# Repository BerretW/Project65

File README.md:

# Project65 — SBC 65C02 IRQ BigBoard

A fully custom **W65C02-based single-board computer** featuring an 8-priority-level IRQ subsystem, three ISA-8 expansion slots, a PS/2 keyboard interface, RS-232 serial port, and a complete firmware stack — including an interactive OS with a RAM-disk filesystem. Accompanied by a **full-featured Rust emulator** with a terminal UI and an **FPGA VGA + audio controller** (`APARTS_BUS`) for Intel MAX 10.

---

## Features

- **CPU:** W65C02S @ up to 8 MHz (jumper-selectable from 32 MHz main oscillator)
- **Memory:** 64 KB total — 32 KB lower RAM + 32 KB upper RAM + 8 KB EEPROM ROM
- **Serial:** R6551 ACIA with a 1.8432 MHz crystal for accurate baud rates
- **Parallel I/O:** 2× W65C22S VIA controllers (keyboard polling + parallel port)
- **PS/2 Keyboard:** ATtiny26 co-processor bridge
- **Interrupt system:** 74HC148 priority encoder + 74HC574 latch — 8 prioritized IRQ lines + NMI
- **Expansion:** 3× ISA-8 slots (TMS9918A, GameDuino, APARTS_BUS FPGA card)
- **FPGA video/audio:** `APARTS_BUS` — VGA 640×480, external SRAM framebuffer, font RAM, 4-ch DDS/ADSR → PCM5102A I²S
- **Firmware:** Two build targets — minimal bootloader and full AppartusOS
- **Emulator:** Rust TUI emulator (`p65emu`) with cycle-accurate peripherals

---

## Repository Structure

```text
Project65/
├── Eagle/              # PCB schematics and board layouts (Eagle CAD)
│   ├── SBC_65C02_IRQ_BigBoard_v10-2-1.*
│   ├── EXP_TMS9918A_V1.*
│   └── EXP_GameDuino_V1.*
├── Firmware/           # 65C02 firmware (cc65 / ca65 toolchain)
│   ├── src/            # Assembly + C sources (drivers, OS, shell, EWOZ)
│   │   └── os/         # AppartusOS modules
│   ├── config/         # ld65 linker configurations
│   ├── output/         # Build artifacts (*.bin, *.map)
│   ├── build_minimal.bat
│   └── build_appartus.bat
├── emulator/           # Rust emulator (p65emu)
│   └── src/            # cpu, bus, ram, rom, acia, via, irq_latch, tui
├── aprts_vga/          # APARTS_BUS FPGA RTL (Verilog) + Quartus + sim
│   ├── aprts_bus.v     # Top-level 6502 bus interface
│   ├── vga_timing.v    # VGA 640×480 @ 60 Hz timing (25 MHz)
│   ├── vga_video_gen.v # Graphics/text pixel path + font RAM
│   ├── sram_controller.v
│   ├── aprts_audio.v   # 4-ch DDS/ADSR + I²S (PCM5102A)
│   ├── 10M02_test.qsf  # Quartus project (MAX 10 10M02SCE144C8G)
│   └── sim/            # ModelSim / Icarus testbenches
├── GAL/                # Glue logic (PLD)
├── tools/
│   ├── uploader.py     # Python/tkinter firmware uploader (COM or TCP)
│   ├── aprts_vga/      # 6502 demo for FPGA VGA
│   ├── audio/          # Audio driver + samples (ca65)
│   └── …               # hello, mem_mon, vera_test, vga_test, …
└── CLAUDE.md           # Full hardware reference (address map, ICs, bugs)
```

---

## Hardware Overview

| Reference | Part | Description |
| --------- | ---- | ----------- |
| IC4 | W65C02SP | Main CPU (CMOS 65C02, DIP-40) |
| IC5 | AT28C64B | 8 KB EEPROM — ROM (`$E000–$FFFF`) |
| IC6 | 62256 | 32 KB SRAM — lower RAM (`$0000–$7FFF`) |
| IC7 | 62256 | 32 KB SRAM — upper RAM (`$8000–$BFFF`) |
| IC8 | DS1233 | Power-on reset supervisor |
| IC16 | W65C22S6TP | VIA #2 (`$CC80`) — parallel port JP8, generates **IRQ1** |
| IC18 | W65C22S6TP | VIA #1 (`$CC00`) — ATtiny26 keyboard bridge, generates **NMI** |
| IC19 | R6551 | ACIA serial (`$C800–$CBFF`) |
| IC14 | ATtiny26 | PS/2 keyboard co-processor (PB3=CLK, PB4=DATA) |
| U$1 | MCP2221A | USB-C ↔ UART/I²C bridge |
| IC9/IC11 | 74HCT139N | Two-stage address decoder |
| IC17 | 74HC148N | 8→3 priority IRQ encoder |
| IC27 | 74HC574N | IRQ status latch (readable at `$C480`) |
| QG1 | 32 MHz | Main system oscillator |
| Q1 | 1.8432 MHz | ACIA baud-rate crystal |
| X1–X3 | ISA-8 slots | Three 8-bit ISA expansion slots |

### ISA Expansion Cards

| Card | Description |
| ---- | ----------- |
| `EXP_TMS9918A_V1` | TMS9918A video card |
| `EXP_GameDuino_V1` | GameDuino graphics card |
| **APARTS_BUS** (`aprts_vga/`) | FPGA VGA 640×480 + external SRAM + 4-ch audio (MAX 10) |

---

## Address Map

```text
$0000–$7FFF   IC6 SRAM — lower 32 KB       (!CS = A15 low)
$8000–$BFFF   IC7 SRAM — upper 32 KB       (!CS = !HRAM_CS)
$C000–$C3FF   VERA / ISA video             (!VERA_CS)
$C400–$C7FF   IRQ latch                    read $C480–$C4FF / ack $C400–$C47F
$C800–$CBFF   ACIA R6551
$CC00–$CC7F   VIA1 (IC18) — keyboard/NMI
$CC80–$CCFF   VIA2 (IC16) — parallel/IRQ1
$CD00–$CDFF   ISA DEV0
$CE00–$CEFF   ISA DEV1
$CF00–$CFFF   ISA DEV2   ← typical APARTS_BUS decode (tools use $CF00 / $CE00)
$D000–$DFFF   ISA extended
$E000–$FFFF   EEPROM ROM (8 KB)
```

### IRQ Priority Table

| Level | Signal | Source |
| ----- | ------ | ------ |
| 0 (highest) | IRQ0 | R6551 ACIA |
| 1 | IRQ1 | VIA2 (IC16, `$CC80`) |
| 2–6 | IRQ2–6 | ISA slots |
| 7 (lowest) | IRQ7 | Button S1 |
| — | **NMI** | **VIA1 (IC18, `$CC00`)** |

---

## APARTS_BUS — FPGA VGA & Audio (`aprts_vga/`)

RTL controller for the 6502/ISA bus: **VGA output**, **external SRAM framebuffer (up to 512 KB / 19-bit address)**, **internal font RAM**, and a **4-channel synthesizer** driving a **PCM5102A** over I²S.

Detailed programmer manual: [`aprts_vga/README.md`](aprts_vga/README.md).

### Target & RTL modules

| Item | Value |
| ---- | ----- |
| FPGA | Intel **MAX 10** — `10M02SCE144C8G` |
| Quartus project | `aprts_vga/10M02_test.qsf` |
| Top entity | `aprts_bus` |
| Pixel clock | **25 MHz** — VGA **640×480 @ 60 Hz** |

| File | Module | Role |
| ---- | ------ | ---- |
| `aprts_bus.v` | `aprts_bus` | Top: 4-bit port decode, CPU R/W, submodule wiring |
| `vga_timing.v` | `vga_timing` | H/V counters, HSYNC/VSYNC, `video_on` |
| `vga_video_gen.v` | `vga_video_gen` | Graphics/text RGB, font RAM (128×8 = 1024 B), cursor blink |
| `sram_controller.v` | `sram_controller` | CPU ↔ VGA arbiter, hardware clear engine |
| `aprts_audio.v` | `aprts_audio` | 4-ch DDS + ADSR, I²S (`pcm_bck` / `pcm_din` / `pcm_lrck`) |

### External interfaces (from `aprts_bus`)

```text
6502 bus:   n_reset, n_mem_w, n_mem_r, lv_cs, clk, lv_addr[3:0], lv_data[7:0]
VGA:        red[2:0], green[2:0], blue[2:0], hsync, vsync
SRAM:       sram_addr[18:0], sram_data[7:0], sram_ce_n, sram_oe_n, sram_we_n
Audio I²S:  pcm_bck, pcm_din, pcm_lrck, pcm_sck
```

### Register map (ports `$0`–`$F` relative to card base)

| Port | Write | Read |
| ---- | ----- | ---- |
| `$0` | Background color RGB332 | `reg_bg_color` |
| `$1` | Address / cursor hi (`addr_hi`) | same |
| `$2` | Address mid (`addr_mid`) | same |
| `$3` | Address lo (`addr_lo`) | same |
| `$4` | Data → SRAM / font / text cell | Data ← SRAM / font |
| `$5` | Audio register index (`0x00`–`0x17`) | current index |
| `$6` | Audio register data (index auto-inc) | selected audio reg |
| `$D` | Mode | current mode |
| `$F` | Start SRAM clear (any value) | status: bit0 = `addr_ready` |

CPU SRAM pointer is 19-bit: `{addr_hi[2:0], addr_mid, addr_lo}`. After each write to port `$4` (except font mode `$0D`) the address **auto-increments**.

**Background / pixel color:** `[7:5]` R, `[4:2]` G, `[1:0]` B (expanded to 3 bits in HW).

### Mode register (`$D`)

| Value | Behavior |
| ----- | -------- |
| `$00`–`$0C` | Graphics — linear framebuffer from external SRAM |
| `$01` | Text 80×60, static cursor |
| `$02` | Text 80×60, blinking cursor (~2 Hz) |
| `$0D` | Font edit — R/W internal `font_mem` via port `$4` |
| `$0E` | Hardware logic reset (counters, audio, registers) |
| `$0F` | Blank screen (force black) |

Text buffer uses the first **4800** bytes of SRAM (`80×60`, `$0000`–`$12BF`). Font RAM: **128 characters × 8 rows**.

### SRAM clear & status (`$F`)

- **Write:** starts hardware fill of external SRAM with zeros (clear range through `$4AFFF` in RTL).
- **Read bit 0 (`addr_ready`):** `1` = ready for CPU access; `0` = clear/write busy. Poll before further writes.

### Audio (ports `$5` / `$6`)

Four independent DDS channels mixed to I²S (PCM5102A). Sample rate in driver notes: **~48.828 kHz**.

Per channel (base offsets for ch0; +3 per channel for ch1–3):

| Index | Register |
| ----- | -------- |
| `+0` / `+1` | Frequency lo / hi |
| `+2` | Volume |
| `$0C`–`$0F` | Control: wave `[2:0]`, ADSR enable `[3]`, gate/note-on `[4]` |
| `$10`–`$17` | ADSR Attack/Decay and Sustain/Release pairs |

Waveforms: `0` square, `1` triangle, `2` saw, `3` sine, `4` trapezoid. Writing `$6` auto-increments the audio index.

### Simulation (`aprts_vga/sim/`)

| File | Purpose |
| ---- | ------- |
| `tb_aprts_bus.v` | Integration test of full `aprts_bus` |
| `tb_vga_timing.v` | VGA timing unit test |
| `tb_aprts_audio.v` | Audio registers + I²S clocks |
| `sram_model.v` | Behavioral 512 KB SRAM |
| `run_msim.bat` / `run_msim.do` | ModelSim / Questa-Intel |
| `run_iverilog.bat` | Icarus Verilog |

```bat
cd aprts_vga\sim
run_msim.bat
rem or: run_iverilog.bat
```

See [`aprts_vga/sim/README.md`](aprts_vga/sim/README.md).

### Host-side tools

| Path | Description |
| ---- | ----------- |
| `tools/aprts_vga/` | ca65 demo (`demo.asm`) — base often `$CF00` |
| `tools/audio/` | Audio includes (`audio.inc65`) and samples — ports `$5`/`$6` on card base |

Exact ISA slot base (`$CD00` / `$CE00` / `$CF00`) depends on which DEV chip-select the card is wired to.

---

## Firmware

### Prerequisites

- [cc65](https://cc65.github.io/) toolchain (`cc65`, `ca65`, `ld65`) on `PATH`

### Minimal Build

ACIA serial + EWOZ (WozMon) monitor + serial bootloader (loads to `$6000`).  
No keyboard, VDP, SPI, SD, GameDuino, or SAA1099 dependencies.

```bat
cd Firmware
build_minimal.bat
```

Output: `Firmware/output/MIN_ROM.bin` (8 KB, write to EEPROM IC5)

### AppartusOS Build

Full OS: ACIA + EWOZ (`MON` command) + Intel HEX loader + interactive shell + RAM-disk FS.

```bat
cd Firmware
build_appartus.bat
```

Output: `Firmware/output/APPARTUS_OS.bin` (8 KB, write to EEPROM IC5)

### AppartusOS Shell Commands

```text
HELP / ?                   — help
VER                        — OS version
DIR                        — list RAM-disk files
FREE                       — show free space
FORMAT                     — reinitialize RAM disk (requires Y confirmation)
LOAD                       — receive Intel HEX via ACIA
SAVE <name> <addr> <size>  — save RAM region to RAM disk (hex addresses)
DEL  <name>                — delete file
RUN  <name>                — execute file (program can RTS back to shell)
MON                        — EWOZ / WozMon monitor
RESET                      — soft reset ($FF00)
```

### RAM Disk Layout (`$6000–$BFFF`, 24 KB)

```text
$6000–$600F   Header: "APOS" + num_files + free_ptr
$6010–$610F   Directory: 16 entries × 16 bytes
              +0 name[8]  +8 load_addr  +10 size  +12 flags  +13 stor_addr
$6110–$BFFF   File data (~24 KB usable)
```

### Firmware Memory Map (ROM, `$E000–$FFFF`)

```text
ZP:      $0000–$00FF   (zero page; cc65 $00–$1F, EWOZ $24–$30, ihex $38–$3E, OS $40–$4E)
RAM:     $0200–$5FFF   (working RAM; stack at $5FFF growing down)
ROM:     $E000–$FFFF   (EEPROM, fill $FF)
JMPTBL:  $FF00         (BIOS-style jump table)
VECTORS: $FFFA         (NMI / RESET / IRQ vectors)
```

---

## Emulator — p65emu

A cycle-accurate Rust emulator with a ratatui terminal UI.

### Build Requirements

- [Rust toolchain](https://rustup.rs/) (stable)

### Build & Run

```sh
cargo run --manifest-path emulator/Cargo.toml -- [ROM.bin] [-s SPEED_HZ] [-p TCP_PORT]
```

| Flag | Default | Description |
| ---- | ------- | ----------- |
| `ROM.bin` | — | ROM image to load at `$E000` |
| `-s SPEED_HZ` | `1000000` | Emulation speed in Hz |
| `-p TCP_PORT` | `6551` | TCP serial port (0 = disabled) |
| `--family` | `HCT` | Logic family timing model (`LS`, `ALS`, `HCT`, `HC`, `AC`, `ACT`) |

### Emulated Components

| Module | Hardware |
| ------ | -------- |
| `cpu.rs` | W65C02 — fetch/decode/execute + NMI/IRQ |
| `ram.rs` | IC6 + IC7 SRAM |
| `rom.rs` | 8 KB EEPROM |
| `acia.rs` | R6551 — TX/RX queues shared with TUI and TCP |
| `via.rs` | VIA1 (`$CC00`) + VIA2 (`$CC80`) — T1/T2 timers |
| `irq_latch.rs` | 74HC574 latch + 74HC148 encoder |
| `tms9918a.rs` | TMS9918A video (minifb window) |
| `saa1099.rs` | SAA1099 audio (rodio) |

### TUI Keyboard Shortcuts

| Key | Action |
| --- | ------ |
| F2 | Single step |
| F3 | Run / Pause |
| F4 | Reset CPU |
| F5–F9 | Speed: 1K / 10K / 100K / 1M / MAX Hz |
| +/- | Speed ×2 / ÷2 |
| Tab | Memory view: ZP / RAM / HiRAM / I/O / ROM / Addr |
| Shift+Tab | Right panel: CPU / VIA1 / VIA2 / ACIA / IRQ |
| PgUp/PgDn | Scroll memory |
| Shift+Pg | Scroll terminal |
| Ctrl+O | File browser — load ROM or RAM image |
| Ctrl+G | Jump to hex address in memory dump |
| Ctrl+M | Edit byte at address |
| Ctrl+R | Edit CPU registers (A/X/Y/SP/PC/P) |
| F10 / Ctrl+Q | Quit |

The TCP serial port (default `127.0.0.1:6551`) allows PuTTY, netcat, or `uploader.py` to connect as if it were real hardware.

---

## Tools

### tools/uploader.py

Python/tkinter GUI for uploading firmware to the real board or the emulator.

**Dependencies:**

```sh
pip install pyserial
```

**Connection modes:**

- **COM port** — real hardware (19200 Bd, 8N1)
- **TCP** — emulator (`127.0.0.1:6551`)

**Bootloader protocol:**

| Command | Action |
| ------- | ------ |
| `w` | Raw binary upload — exactly 8192 bytes → `$6000–$7FFF` |
| `h` | Intel HEX upload (any address) |
| `s` | Jump to `$6000` (run program) |
| `m` | Enter EWOZ / WozMon monitor |
| `^R` (`$12`) | Soft-restart bootloader |

### Other tools

| Path | Description |
| ---- | ----------- |
| `tools/aprts_vga/` | APARTS_BUS VGA demo for AppartusOS |
| `tools/audio/` | 4-channel FPGA audio driver and samples |
| `tools/hello/` | Sample user program |
| `tools/ihex_gen.py` | Intel HEX helper |
| `tools/espi_update_fpga.py` | FPGA update helper |
| `tools/vera_test/`, `tools/vga_test/` | Video experiments |

---

## Typical Workflow

```sh
# 1. Build firmware
cd Firmware && build_appartus.bat

# 2. Start emulator
cargo run --manifest-path emulator/Cargo.toml -- Firmware/output/APPARTUS_OS.bin

# 3. In emulator terminal — send a program via Intel HEX
> LOAD
  (paste or send .hex file via uploader.py over TCP)

# 4. Save and run
> SAVE HELLO 6090 0100
> DIR
> RUN HELLO
```

FPGA RTL / sim workflow:

```bat
cd aprts_vga\sim
run_msim.bat
```

---

## Known Issues

| # | Status | Description |
| - | ------ | ----------- |
| 1 | ✅ Fixed | `_nmi_init` in `utils.asm` — NMI Timer1 initialization correctly configures VIA1 (IC18) at $CC00 |
| 2 | ✅ Fixed | NMI ISR correctly reloads VIA1 (IC18) T1 counter — verified in `interrupts.asm:19` |
| 3 | ✅ Fixed | PS/2 keyboard driver in `pckybd.asm:25–28` — now correctly reads from VIA1 (IC18, ATtiny26) |
| 4 | ✅ Fixed | `VDP_MODE0 = $C000` — correctly placed in ISA I/O space, no longer conflicts with IC6 RAM |

All critical hardware bugs have been resolved.

---

## Hardware Files

| File | Description |
| ---- | ----------- |
| `Eagle/SBC_65C02_IRQ_BigBoard_v10-2-1.csv` | Current BOM / netlist |
| `Eagle/SBC_65C02_IRQ_BigBoard_v9-1-3.sch` | Main schematic (Eagle) |
| `Eagle/SBC_65C02_IRQ_BigBoard_v9-1-3.brd` | Main PCB layout (Eagle) |
| `Eagle/EXP_TMS9918A_V1.sch/.brd` | TMS9918A ISA video card |
| `Eagle/EXP_GameDuino_V1.sch/.brd` | GameDuino ISA graphics card |
| `aprts_vga/*.v` | APARTS_BUS FPGA RTL (VGA + SRAM + audio) |
| `aprts_vga/10M02_test.qsf` | Quartus pinout / project for MAX 10 |

Full hardware documentation (address decoding logic, IC cross-reference, IRQ system) is in [`CLAUDE.md`](CLAUDE.md).  
FPGA register-level docs: [`aprts_vga/README.md`](aprts_vga/README.md).

---

## License

See [`Firmware/LICENSE`](Firmware/LICENSE).

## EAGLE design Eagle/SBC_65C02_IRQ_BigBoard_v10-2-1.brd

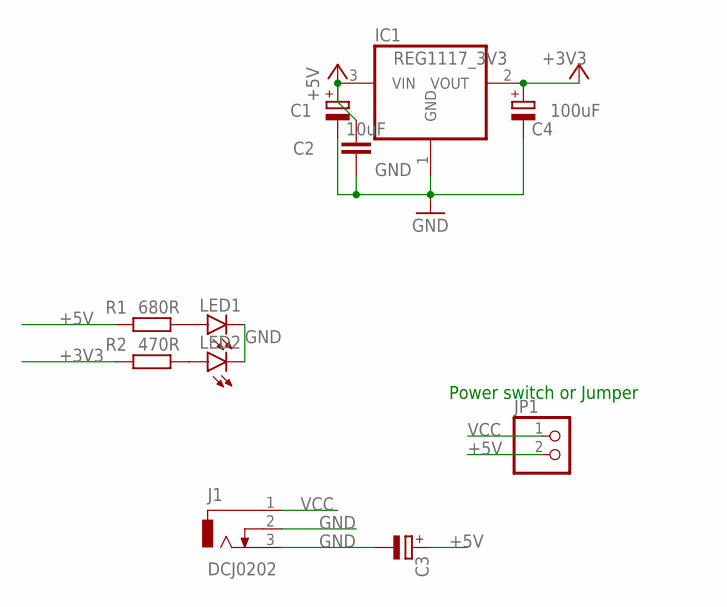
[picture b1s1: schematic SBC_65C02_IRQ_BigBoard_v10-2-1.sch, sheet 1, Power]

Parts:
C1: 10uF; E2,5-5
C2: C-EU050-035X075; C050-035X075
C3: CPOL-EUE2.5-5; E2,5-5
C4: 100uF; E2,5-5
IC1: REG1117_3V3; SOT223
J1: DCJ0202
JP1: PINHD-1X2; 1X02
LED1, LED2: LED5MM
R1: 680R; 0207/10
R2: 470R; 0207/10

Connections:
+3V3: C4.+, IC1.2 (VOUT), R2.2
+5V: C1.+, C2.1, C3.+, IC1.3 (VIN), JP1.2, R1.2; also elsewhere on the board
GND: C1.-, C2.2, C3.-, C4.-, IC1.1 (GND), J1.2, J1.3, LED1.K (C), LED2.K (C); also elsewhere on the board
unnamed: LED1.A, R1.1
unnamed: LED2.A, R2.1
VCC: J1.1, JP1.1

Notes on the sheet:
Power switch or Jumper

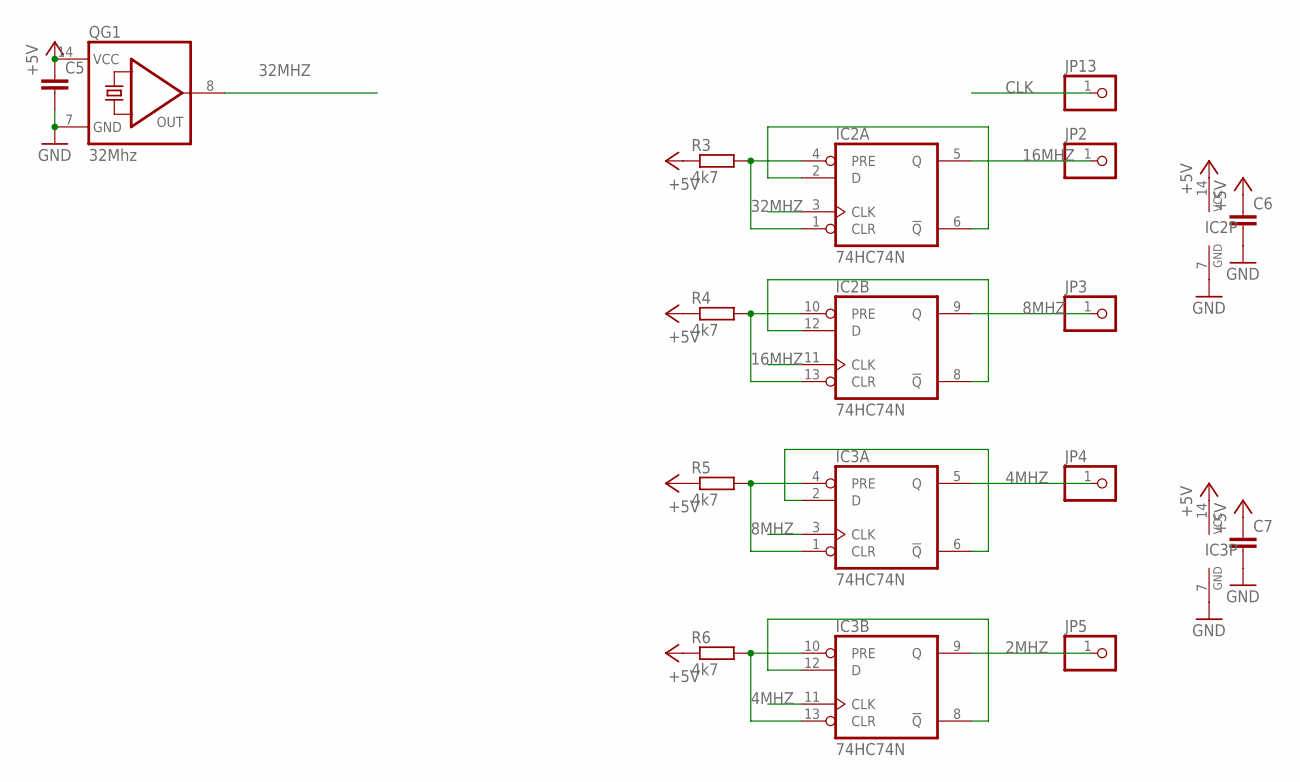
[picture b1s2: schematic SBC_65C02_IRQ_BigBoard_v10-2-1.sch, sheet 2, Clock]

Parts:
C5, C6, C7: C-EU050-025X075; C050-025X075
IC2, IC3: 74HC74N; DIL14
JP2, JP3, JP4, JP5, JP13: PINHD-1X1; 1X01
QG1: 32Mhz; DIL14S
R3, R4, R5, R6: 4k7; 0204/7

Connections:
2MHZ: IC3.9 (Q), JP5.1
4MHZ: IC3.5 (Q), IC3.11 (CLK), JP4.1
8MHZ: IC2.9 (Q), IC3.3 (CLK), JP3.1
16MHZ: IC2.5 (Q), IC2.11 (CLK), JP2.1
32MHZ: IC2.3 (CLK), QG1.8 (OUT); also elsewhere on the board
+5V: C5.1, C6.1, C7.1, IC2.14 (VCC), IC3.14 (VCC), QG1.14 (VCC), R3.1, R4.1, R5.1, R6.1; also elsewhere on the board
CLK: JP13.1; also elsewhere on the board
GND: C5.2, C6.2, C7.2, IC2.7 (GND), IC3.7 (GND), QG1.7 (GND); also elsewhere on the board
unnamed: IC2.2 (D), IC2.6 (!Q)
unnamed: IC2.8 (!Q), IC2.12 (D)
unnamed: IC2.1 (CLR), IC2.4 (PRE), R3.2
unnamed: IC2.10 (PRE), IC2.13 (CLR), R4.2
unnamed: IC3.2 (D), IC3.6 (!Q)
unnamed: IC3.1 (CLR), IC3.4 (PRE), R5.2
unnamed: IC3.8 (!Q), IC3.12 (D)
unnamed: IC3.10 (PRE), IC3.13 (CLR), R6.2

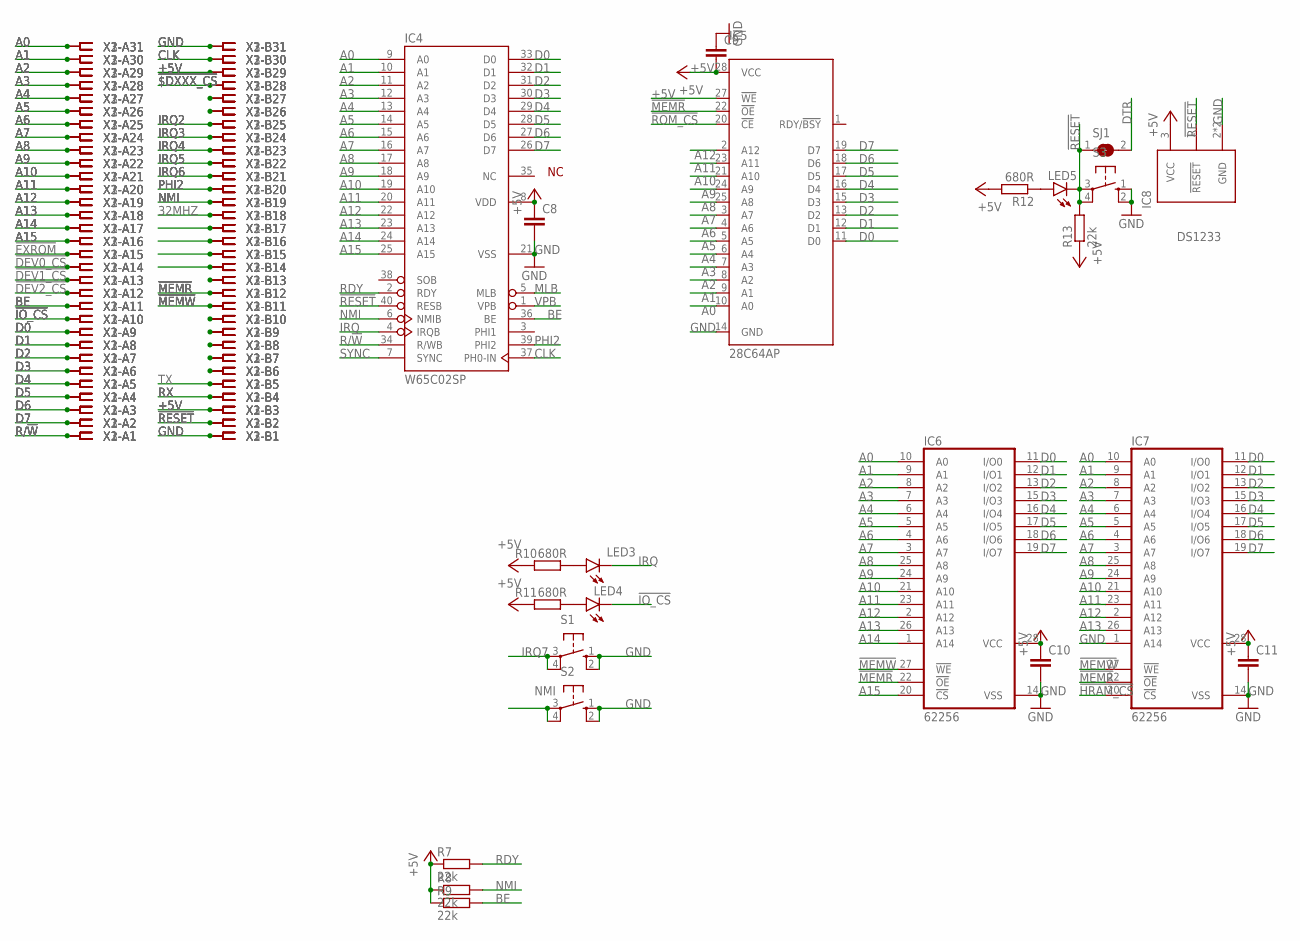
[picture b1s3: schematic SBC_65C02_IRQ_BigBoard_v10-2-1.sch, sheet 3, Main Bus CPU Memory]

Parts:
C8, C9, C10, C11: C-EU050-025X075; C050-025X075
IC4: W65C02SP; DIL40
IC5: 28C64AP; DIL28-6
IC6, IC7: 62256; DIL28-6
IC8: DS1233; SOT223
LED3, LED4, LED5: LED5MM
R7, R8, R9, R13: 22k; 0207/10
R10, R11, R12: 680R; 0207/10
S1, S2, S3: 10-XX; B3F-10XX
SJ1: SJ
X1, X2, X3: ISA-SLOT; ISA-8

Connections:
32MHZ: X1.B18, X2.B18, X3.B18; also elsewhere on the board
!$DXXX_CS: X1.B28, X2.B28, X3.B28; also elsewhere on the board
!DEV0_CS: X1.A14, X2.A14, X3.A14; also elsewhere on the board
!DEV1_CS: X1.A13, X2.A13, X3.A13; also elsewhere on the board
!DEV2_CS: X1.A12, X2.A12, X3.A12; also elsewhere on the board
!EXROM: X1.A15, X2.A15, X3.A15; also elsewhere on the board
!HRAM_CS: IC7.20 (!CS); also elsewhere on the board
!IO_CS: LED4.K (C), X1.A10, X2.A10, X3.A10; also elsewhere on the board
!MEMR: IC5.22 (!OE), IC6.22 (!OE), IC7.22 (!OE), X1.B12, X2.B12, X3.B12; also elsewhere on the board
!MEMW: IC6.27 (!WE), IC7.27 (!WE), X1.B11, X2.B11, X3.B11; also elsewhere on the board
!RESET: IC4.40 (RESB), IC8.1 (!RESET), LED5.K (C), R13.2, S3.3, S3.4 (P1), SJ1.1, X1.B2, X2.B2, X3.B2; also elsewhere on the board
!ROM_CS: IC5.20 (!CE); also elsewhere on the board
+5V: C8.1, C9.2, C10.1, C11.1, IC4.8 (VDD), IC5.27 (!WE), IC5.28 (VCC), IC6.28 (VCC), IC7.28 (VCC), IC8.3 (VCC), R7.1, R8.1, R9.1, R10.2, R11.2, R12.2, R13.1, X1.B3, X1.B29, X2.B3, X2.B29, X3.B3, X3.B29; also elsewhere on the board
A0: IC4.9 (A0), IC5.10 (A0), IC6.10 (A0), IC7.10 (A0), X1.A31, X2.A31, X3.A31; also elsewhere on the board
A1: IC4.10 (A1), IC5.9 (A1), IC6.9 (A1), IC7.9 (A1), X1.A30, X2.A30, X3.A30; also elsewhere on the board
A2: IC4.11 (A2), IC5.8 (A2), IC6.8 (A2), IC7.8 (A2), X1.A29, X2.A29, X3.A29; also elsewhere on the board
A3: IC4.12 (A3), IC5.7 (A3), IC6.7 (A3), IC7.7 (A3), X1.A28, X2.A28, X3.A28; also elsewhere on the board
A4: IC4.13 (A4), IC5.6 (A4), IC6.6 (A4), IC7.6 (A4), X1.A27, X2.A27, X3.A27; also elsewhere on the board
A5: IC4.14 (A5), IC5.5 (A5), IC6.5 (A5), IC7.5 (A5), X1.A26, X2.A26, X3.A26
A6: IC4.15 (A6), IC5.4 (A6), IC6.4 (A6), IC7.4 (A6), X1.A25, X2.A25, X3.A25
A7: IC4.16 (A7), IC5.3 (A7), IC6.3 (A7), IC7.3 (A7), X1.A24, X2.A24, X3.A24; also elsewhere on the board
A8: IC4.17 (A8), IC5.25 (A8), IC6.25 (A8), IC7.25 (A8), X1.A23, X2.A23, X3.A23; also elsewhere on the board
A9: IC4.18 (A9), IC5.24 (A9), IC6.24 (A9), IC7.24 (A9), X1.A22, X2.A22, X3.A22; also elsewhere on the board
A10: IC4.19 (A10), IC5.21 (A10), IC6.21 (A10), IC7.21 (A10), X1.A21, X2.A21, X3.A21; also elsewhere on the board
A11: IC4.20 (A11), IC5.23 (A11), IC6.23 (A11), IC7.23 (A11), X1.A20, X2.A20, X3.A20; also elsewhere on the board
A12: IC4.22 (A12), IC5.2 (A12), IC6.2 (A12), IC7.2 (A12), X1.A19, X2.A19, X3.A19; also elsewhere on the board
A13: IC4.23 (A13), IC6.26 (A13), IC7.26 (A13), X1.A18, X2.A18, X3.A18; also elsewhere on the board
A14: IC4.24 (A14), IC6.1 (A14), X1.A17, X2.A17, X3.A17; also elsewhere on the board
A15: IC4.25 (A15), IC6.20 (!CS), X1.A16, X2.A16, X3.A16; also elsewhere on the board
BE: IC4.36 (BE), R9.2, X1.A11, X2.A11, X3.A11
CLK: IC4.37 (PH0-IN), X1.B30, X2.B30, X3.B30; also elsewhere on the board
CS_1: X1.B27, X2.B27, X3.B27
CS_2: X1.B26, X2.B26, X3.B26
D0: IC4.33 (D0), IC5.11 (D0), IC6.11 (I/O0), IC7.11 (I/O0), X1.A9, X2.A9, X3.A9; also elsewhere on the board
D1: IC4.32 (D1), IC5.12 (D1), IC6.12 (I/O1), IC7.12 (I/O1), X1.A8, X2.A8, X3.A8; also elsewhere on the board
D2: IC4.31 (D2), IC5.13 (D2), IC6.13 (I/O2), IC7.13 (I/O2), X1.A7, X2.A7, X3.A7; also elsewhere on the board
D3: IC4.30 (D3), IC5.15 (D3), IC6.15 (I/O3), IC7.15 (I/O3), X1.A6, X2.A6, X3.A6; also elsewhere on the board
D4: IC4.29 (D4), IC5.16 (D4), IC6.16 (I/O4), IC7.16 (I/O4), X1.A5, X2.A5, X3.A5; also elsewhere on the board
D5: IC4.28 (D5), IC5.17 (D5), IC6.17 (I/O5), IC7.17 (I/O5), X1.A4, X2.A4, X3.A4; also elsewhere on the board
D6: IC4.27 (D6), IC5.18 (D6), IC6.18 (I/O6), IC7.18 (I/O6), X1.A3, X2.A3, X3.A3; also elsewhere on the board
D7: IC4.26 (D7), IC5.19 (D7), IC6.19 (I/O7), IC7.19 (I/O7), X1.A2, X2.A2, X3.A2; also elsewhere on the board
DTR: SJ1.2; also elsewhere on the board
GND: C8.2, C9.1, C10.2, C11.2, IC4.21 (VSS), IC5.14 (GND), IC6.14 (VSS), IC7.1 (A14), IC7.14 (VSS), IC8.2 (GND), IC8.4 (GND), S1.1 (S), S1.2 (S1), S2.1 (S), S2.2 (S1), S3.1 (S), S3.2 (S1), X1.B1, X1.B31, X2.B1, X2.B31, X3.B1, X3.B31; also elsewhere on the board
IRQ: IC4.4 (IRQB), LED3.K (C); also elsewhere on the board
IRQ2: X1.B25, X2.B25, X3.B25; also elsewhere on the board
IRQ3: X1.B24, X2.B24, X3.B24; also elsewhere on the board
IRQ4: X1.B23, X2.B23, X3.B23; also elsewhere on the board
IRQ5: X1.B22, X2.B22, X3.B22; also elsewhere on the board
IRQ6: X1.B21, X2.B21, X3.B21; also elsewhere on the board
IRQ7: S1.3, S1.4 (P1); also elsewhere on the board
MLB: IC4.5 (MLB)
unnamed: LED3.A, R10.1
unnamed: LED5.A, R12.1
unnamed: X1.B6, X2.B6, X3.B6
unnamed: X1.B7, X2.B7, X3.B7
unnamed: X1.B8, X2.B8, X3.B8
unnamed: LED4.A, R11.1
unnamed: X1.B9, X2.B9, X3.B9
unnamed: X1.B10, X2.B10, X3.B10
unnamed: X1.B13, X2.B13, X3.B13
unnamed: X1.B14, X2.B14, X3.B14
NMI: IC4.6 (NMIB), R8.2, S2.3, S2.4 (P1), X1.B19, X2.B19, X3.B19; also elsewhere on the board
PHI2: IC4.39 (PHI2), X1.B20, X2.B20, X3.B20; also elsewhere on the board
R/!W: IC4.34 (R/WB), X1.A1, X2.A1, X3.A1; also elsewhere on the board
RDY: IC4.2 (RDY), R7.2
RX: X1.B4, X2.B4, X3.B4; also elsewhere on the board
SPI_MOSI: X1.B17, X2.B17, X3.B17
SPI_NSEL2: X1.B15, X2.B15, X3.B15
SPI_SCLK: X1.B16, X2.B16, X3.B16
SYNC: IC4.7 (SYNC)
TX: X1.B5, X2.B5, X3.B5; also elsewhere on the board
VPB: IC4.1 (VPB)

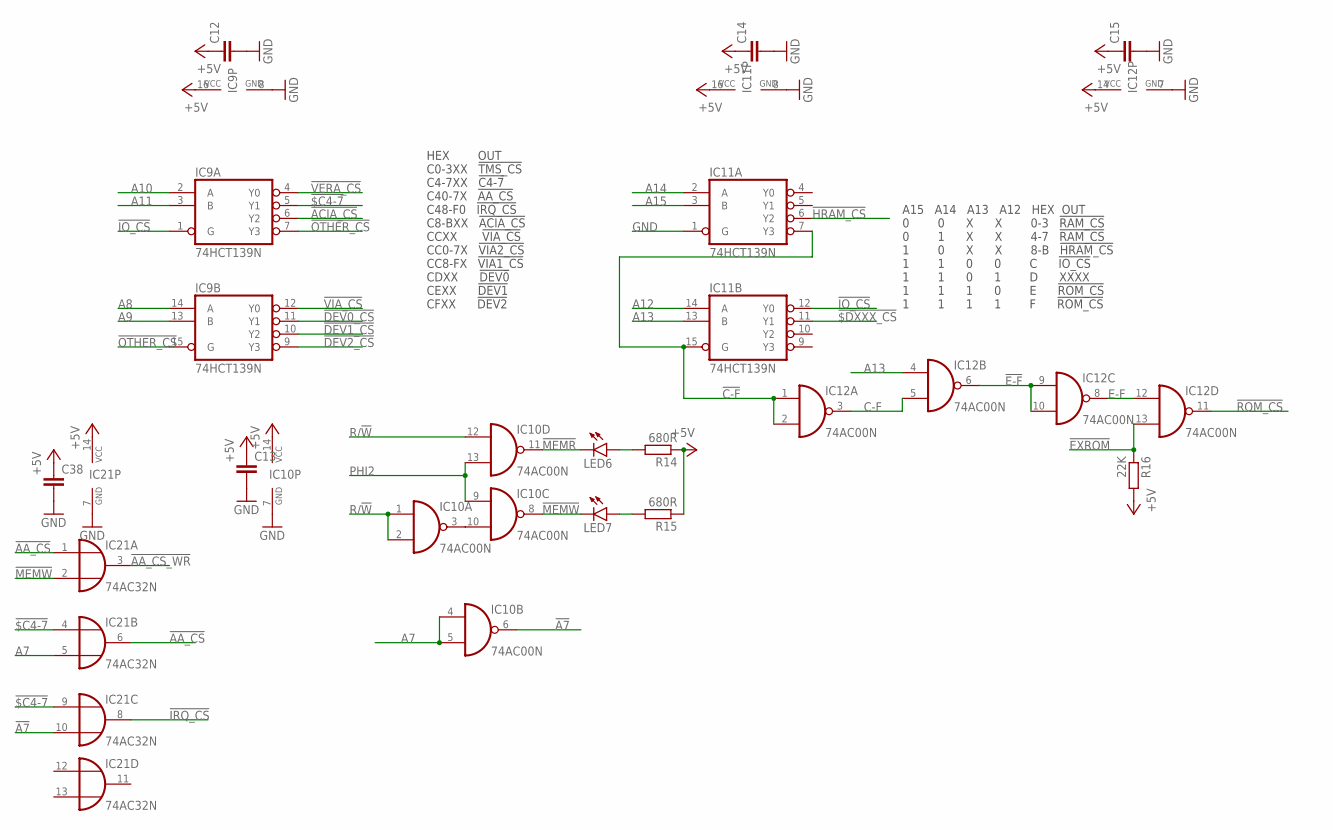
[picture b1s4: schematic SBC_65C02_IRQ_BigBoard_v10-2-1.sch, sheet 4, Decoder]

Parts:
C12, C13, C14, C15, C38: C-EU050-025X075; C050-025X075
IC9, IC11: 74HCT139N; DIL16
IC10, IC12: 74AC00N; DIL14
IC21: 74AC32N; DIL14
LED6, LED7: LED5MM
R14, R15: 680R; 0207/10
R16: 22K; 0207/10

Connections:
!$C4-7: IC9.5 (Y1), IC21.4 (I0), IC21.9 (I0)
!$DXXX_CS: IC11.11 (Y1); also elsewhere on the board
!A7: IC10.6 (O), IC21.10 (I1); also elsewhere on the board
!AA_CS: IC21.1 (I0), IC21.6 (O)
!AA_CS_WR: IC21.3 (O)
!ACIA_CS: IC9.6 (Y2); also elsewhere on the board
!C-F: IC11.7 (Y3), IC11.15 (G), IC12.1 (I0), IC12.2 (I1)
!DEV0_CS: IC9.11 (Y1); also elsewhere on the board
!DEV1_CS: IC9.10 (Y2); also elsewhere on the board
!DEV2_CS: IC9.9 (Y3); also elsewhere on the board
!E-F: IC12.6 (O), IC12.9 (I0), IC12.10 (I1)
!EXROM: IC12.13 (I1), R16.1; also elsewhere on the board
!HRAM_CS: IC11.6 (Y2); also elsewhere on the board
!IO_CS: IC9.1 (G), IC11.12 (Y0); also elsewhere on the board
!IRQ_CS: IC21.8 (O); also elsewhere on the board
!MEMR: IC10.11 (O), LED6.K (C); also elsewhere on the board
!MEMW: IC10.8 (O), IC21.2 (I1), LED7.K (C); also elsewhere on the board
!OTHER_CS: IC9.7 (Y3), IC9.15 (G)
!ROM_CS: IC12.11 (O); also elsewhere on the board
!VERA_CS: IC9.4 (Y0); also elsewhere on the board
!VIA_CS: IC9.12 (Y0); also elsewhere on the board
+5V: C12.1, C13.1, C14.1, C15.1, C38.1, IC9.16 (VCC), IC10.14 (VCC), IC11.16 (VCC), IC12.14 (VCC), IC21.14 (VCC), R14.1, R15.1, R16.2; also elsewhere on the board
A7: IC10.4 (I0), IC10.5 (I1), IC21.5 (I1); also elsewhere on the board
A8: IC9.14 (A); also elsewhere on the board
A9: IC9.13 (B); also elsewhere on the board
A10: IC9.2 (A); also elsewhere on the board
A11: IC9.3 (B); also elsewhere on the board
A12: IC11.14 (A); also elsewhere on the board
A13: IC11.13 (B), IC12.4 (I0); also elsewhere on the board
A14: IC11.2 (A); also elsewhere on the board
A15: IC11.3 (B); also elsewhere on the board
C-F: IC12.3 (O), IC12.5 (I1)
E-F: IC12.8 (O), IC12.12 (I0)
GND: C12.2, C13.2, C14.2, C15.2, C38.2, IC9.8 (GND), IC10.7 (GND), IC11.1 (G), IC11.8 (GND), IC12.7 (GND), IC21.7 (GND); also elsewhere on the board
unnamed: LED6.A, R14.2
unnamed: LED7.A, R15.2
unnamed: IC10.3 (O), IC10.10 (I1)
PHI2: IC10.9 (I0), IC10.13 (I1); also elsewhere on the board
R/!W: IC10.1 (I0), IC10.2 (I1), IC10.12 (I0); also elsewhere on the board

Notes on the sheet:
HEX OUT C0-3XX !TMS_CS C4-7XX !C4-7 C40-7X !AA_CS C48-F0 !IRQ_CS C8-BXX !ACIA_CS CCXX !VIA_CS CC0-7X !VIA2_CS CC8-FX !VIA1_CS CDXX !DEV0 CEXX !DEV1 CFXX !DEV2
A15 A14 A13 A12 HEX OUT 0 0 X X 0-3 !RAM_CS 0 1 X X 4-7 !RAM_CS 1 0 X X 8-B !HRAM_CS 1 1 0 0 C !IO_CS 1 1 0 1 D XXXX 1 1 1 0 E !ROM_CS 1 1 1 1 F !ROM_CS

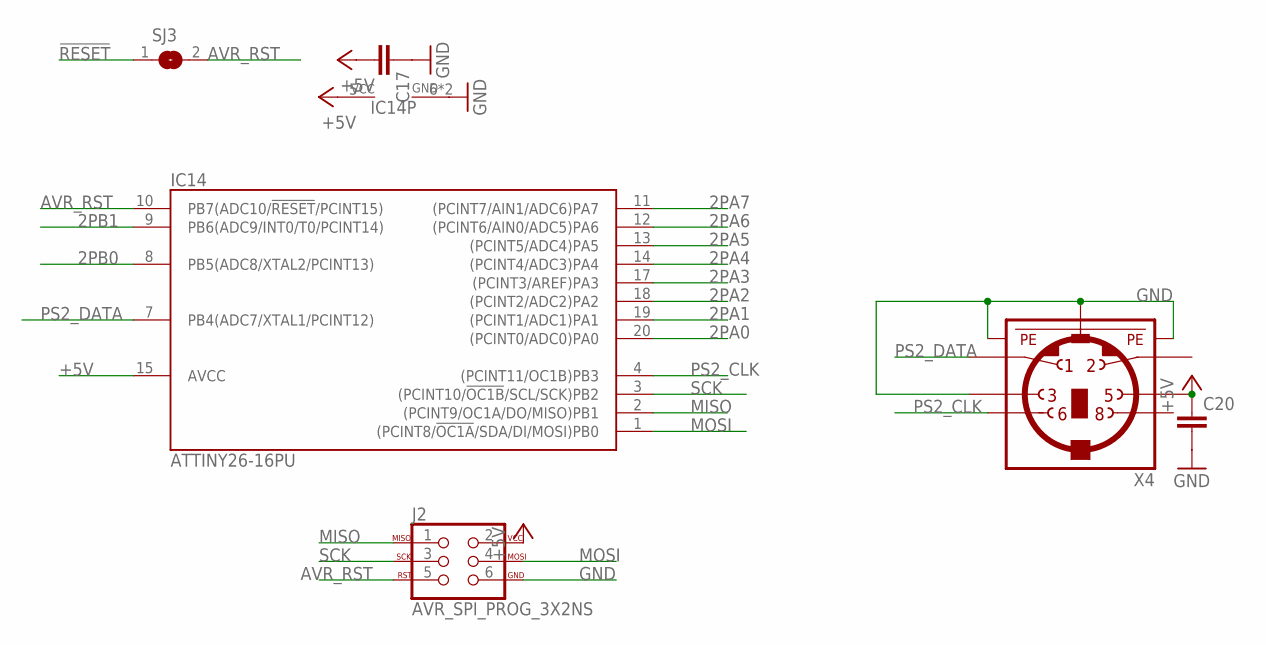
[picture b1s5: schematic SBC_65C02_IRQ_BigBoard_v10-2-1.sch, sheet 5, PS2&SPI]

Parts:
C17, C20: C-EU050-025X075; C050-025X075
IC14: ATTINY26-16PU; DIL20
J2: AVR_SPI_PROG_3X2NS; 2X3-NS
SJ3: SJ
X4: MINI_DIN_6; M_DIN6

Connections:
2PA0: IC14.20 ((PCINT0/ADC0)PA0); also elsewhere on the board
2PA1: IC14.19 ((PCINT1/ADC1)PA1); also elsewhere on the board
2PA2: IC14.18 ((PCINT2/ADC2)PA2); also elsewhere on the board
2PA3: IC14.17 ((PCINT3/AREF)PA3); also elsewhere on the board
2PA4: IC14.14 ((PCINT4/ADC3)PA4); also elsewhere on the board
2PA5: IC14.13 ((PCINT5/ADC4)PA5); also elsewhere on the board
2PA6: IC14.12 ((PCINT6/AIN0/ADC5)PA6); also elsewhere on the board
2PA7: IC14.11 ((PCINT7/AIN1/ADC6)PA7); also elsewhere on the board
2PB0: IC14.8 (PB5(ADC8/XTAL2/PCINT13)); also elsewhere on the board
2PB1: IC14.9 (PB6(ADC9/INT0/T0/PCINT14)); also elsewhere on the board
!RESET: SJ3.1; also elsewhere on the board
+5V: C17.2, C20.1, IC14.5 (VCC), IC14.15 (AVCC), J2.2, X4.5; also elsewhere on the board
AVR_RST: IC14.10 (PB7(ADC10/!RESET!/PCINT15)), J2.5, SJ3.2
GND: C17.1, C20.2, IC14.6 (GND), IC14.16 (GND), J2.6, X4.3, X4.SH1 (PE1), X4.SH2 (PE2), X4.SH3 (PE3); also elsewhere on the board
MISO: IC14.2 ((PCINT9/OC1A/DO/MISO)PB1), J2.1
MOSI: IC14.1 ((PCINT8/!OC1A!/SDA/DI/MOSI)PB0), J2.4
PS2_CLK: IC14.4 ((PCINT11/OC1B)PB3), X4.6
PS2_DATA: IC14.7 (PB4(ADC7/XTAL1/PCINT12)), X4.1
SCK: IC14.3 ((PCINT10/!OC1B!/SCL/SCK)PB2), J2.3

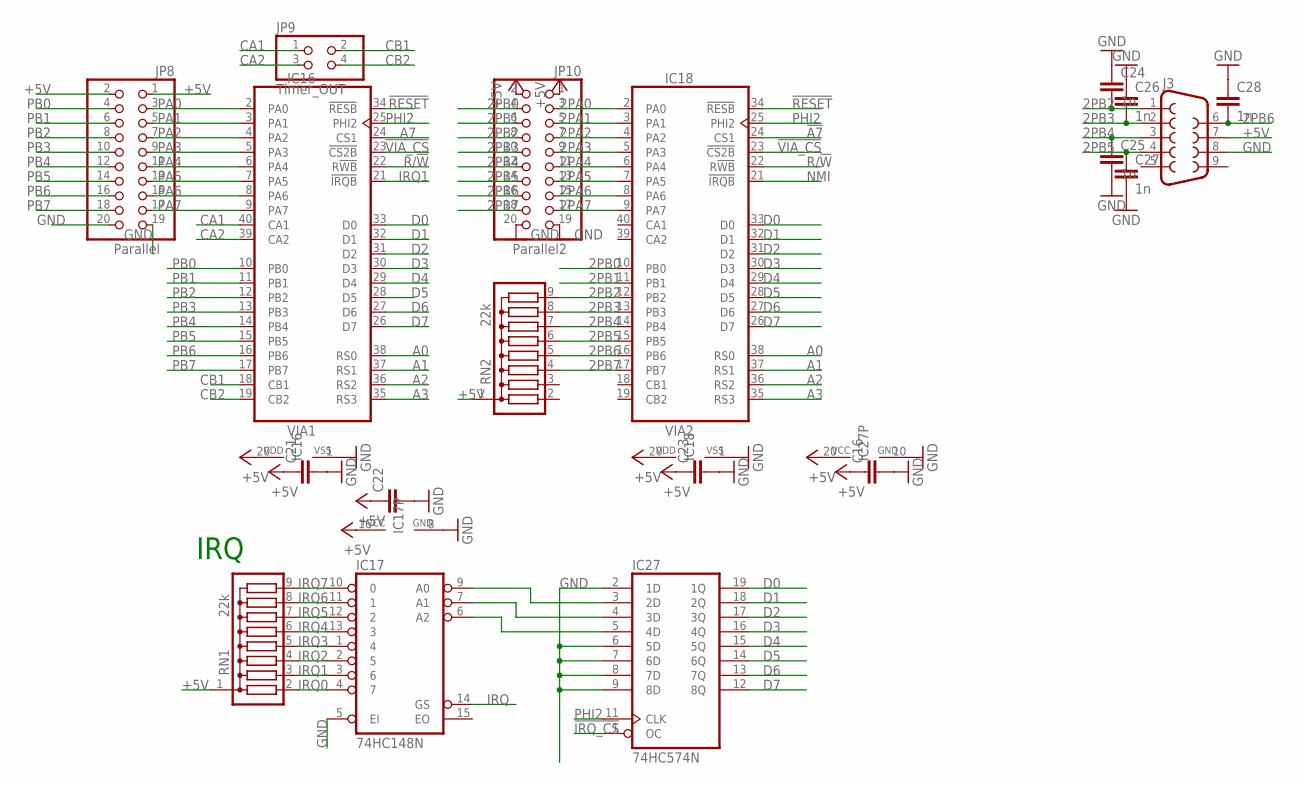
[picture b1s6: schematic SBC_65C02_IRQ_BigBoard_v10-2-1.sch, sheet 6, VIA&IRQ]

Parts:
C16, C21, C22, C23: C-EU050-025X075; C050-025X075
C24, C25, C26, C27, C28: 1n; C050-025X075
IC16: VIA1; DIL40
IC17: 74HC148N; DIL16
IC18: VIA2; DIL40
IC27: 74HC574N; DIL20
J3: DB9MALE; DB9_MALE
JP8: Parallel; 2X10
JP9: Timer_OUT; 2X02
JP10: Parallel2; 2X10
RN1, RN2: 22k; SIL9

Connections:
2PA0: IC18.2 (PA0), JP10.3; also elsewhere on the board
2PA1: IC18.3 (PA1), JP10.5; also elsewhere on the board
2PA2: IC18.4 (PA2), JP10.7; also elsewhere on the board
2PA3: IC18.5 (PA3), JP10.9; also elsewhere on the board
2PA4: IC18.6 (PA4), JP10.11; also elsewhere on the board
2PA5: IC18.7 (PA5), JP10.13; also elsewhere on the board
2PA6: IC18.8 (PA6), JP10.15; also elsewhere on the board
2PA7: IC18.9 (PA7), JP10.17; also elsewhere on the board
2PB0: IC18.10 (PB0), JP10.4; also elsewhere on the board
2PB1: IC18.11 (PB1), JP10.6; also elsewhere on the board
2PB2: C24.2, IC18.12 (PB2), J3.1, JP10.8, RN2.9
2PB3: C26.2, IC18.13 (PB3), J3.2, JP10.10, RN2.8
2PB4: C25.1, IC18.14 (PB4), J3.3, JP10.12, RN2.7
2PB5: C27.1, IC18.15 (PB5), J3.4, JP10.14, RN2.6
2PB6: C28.2, IC18.16 (PB6), J3.6, JP10.16, RN2.5
2PB7: IC18.17 (PB7), JP10.18, RN2.4
!A7: IC18.24 (CS1); also elsewhere on the board
!IRQ_CS: IC27.1 (OC); also elsewhere on the board
!RESET: IC16.34 (!RESB), IC18.34 (!RESB); also elsewhere on the board
!VIA_CS: IC16.23 (!CS2B), IC18.23 (!CS2B); also elsewhere on the board
+5V: C16.1, C21.1, C22.1, C23.1, IC16.20 (VDD), IC17.16 (VCC), IC18.20 (VDD), IC27.20 (VCC), J3.7, JP8.1, JP8.2, JP10.1, JP10.2, RN1.1, RN2.1; also elsewhere on the board
A0: IC16.38 (RS0), IC18.38 (RS0); also elsewhere on the board
A1: IC16.37 (RS1), IC18.37 (RS1); also elsewhere on the board
A2: IC16.36 (RS2), IC18.36 (RS2); also elsewhere on the board
A3: IC16.35 (RS3), IC18.35 (RS3); also elsewhere on the board
A7: IC16.24 (CS1); also elsewhere on the board
CA1: IC16.40 (CA1), JP9.1
CA2: IC16.39 (CA2), JP9.3
CB1: IC16.18 (CB1), JP9.2
CB2: IC16.19 (CB2), JP9.4
D0: IC16.33 (D0), IC18.33 (D0), IC27.19 (1Q); also elsewhere on the board
D1: IC16.32 (D1), IC18.32 (D1), IC27.18 (2Q); also elsewhere on the board
D2: IC16.31 (D2), IC18.31 (D2), IC27.17 (3Q); also elsewhere on the board
D3: IC16.30 (D3), IC18.30 (D3), IC27.16 (4Q); also elsewhere on the board
D4: IC16.29 (D4), IC18.29 (D4), IC27.15 (5Q); also elsewhere on the board
D5: IC16.28 (D5), IC18.28 (D5), IC27.14 (6Q); also elsewhere on the board
D6: IC16.27 (D6), IC18.27 (D6), IC27.13 (7Q); also elsewhere on the board
D7: IC16.26 (D7), IC18.26 (D7), IC27.12 (8Q); also elsewhere on the board
GND: C16.2, C21.2, C22.2, C23.2, C24.1, C25.2, C26.1, C27.2, C28.1, IC16.1 (VSS), IC17.5 (EI), IC17.8 (GND), IC18.1 (VSS), IC27.2 (1D), IC27.6 (5D), IC27.7 (6D), IC27.8 (7D), IC27.9 (8D), IC27.10 (GND), J3.8, JP8.19, JP8.20, JP10.19, JP10.20; also elsewhere on the board
IRQ: IC17.14 (GS); also elsewhere on the board
IRQ0: IC17.4 (7), RN1.2; also elsewhere on the board
IRQ1: IC16.21 (!IRQB), IC17.3 (6), RN1.3
IRQ2: IC17.2 (5), RN1.4; also elsewhere on the board
IRQ3: IC17.1 (4), RN1.5; also elsewhere on the board
IRQ4: IC17.13 (3), RN1.6; also elsewhere on the board
IRQ5: IC17.12 (2), RN1.7; also elsewhere on the board
IRQ6: IC17.11 (1), RN1.8; also elsewhere on the board
IRQ7: IC17.10 (0), RN1.9; also elsewhere on the board
unnamed: IC17.9 (A0), IC27.3 (2D)
unnamed: IC17.7 (A1), IC27.4 (3D)
unnamed: IC17.6 (A2), IC27.5 (4D)
NMI: IC18.21 (!IRQB); also elsewhere on the board
PA0: IC16.2 (PA0), JP8.3
PA1: IC16.3 (PA1), JP8.5
PA2: IC16.4 (PA2), JP8.7
PA3: IC16.5 (PA3), JP8.9
PA4: IC16.6 (PA4), JP8.11
PA5: IC16.7 (PA5), JP8.13
PA6: IC16.8 (PA6), JP8.15
PA7: IC16.9 (PA7), JP8.17
PB0: IC16.10 (PB0), JP8.4
PB1: IC16.11 (PB1), JP8.6
PB2: IC16.12 (PB2), JP8.8
PB3: IC16.13 (PB3), JP8.10
PB4: IC16.14 (PB4), JP8.12
PB5: IC16.15 (PB5), JP8.14
PB6: IC16.16 (PB6), JP8.16
PB7: IC16.17 (PB7), JP8.18
PHI2: IC16.25 (PHI2), IC18.25 (PHI2), IC27.11 (CLK); also elsewhere on the board
R/!W: IC16.22 (R!WB), IC18.22 (R!WB); also elsewhere on the board

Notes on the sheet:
IRQ

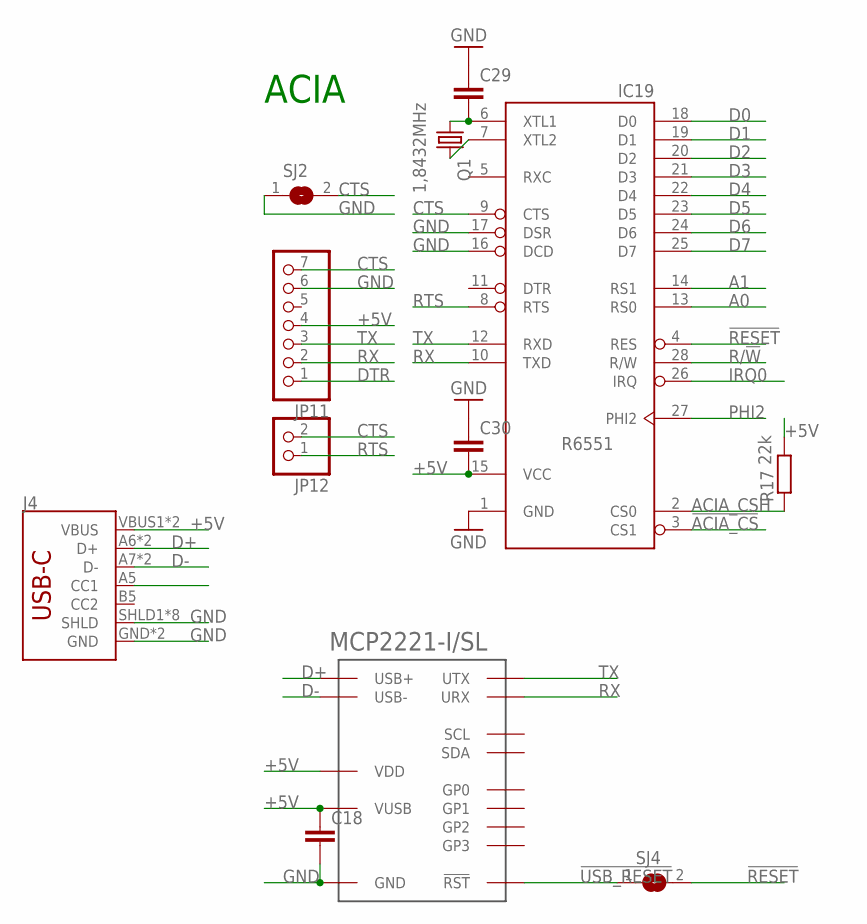
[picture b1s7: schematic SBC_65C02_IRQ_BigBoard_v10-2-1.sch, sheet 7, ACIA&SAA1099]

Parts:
C18, C29, C30: C-EU050-025X075; C050-025X075
IC19: R6551; DIP-28
J4: USB_C2-LAYER; USB-C-16P
JP11: PINHD-1X7; 1X07
JP12: PINHD-1X2; 1X02
Q1: 1,8432MHz; HC49/S
R17: 22k; 0207/10
SJ2, SJ4: SJ
U$1: MCP2221A-I/P; DIL14

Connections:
!ACIA_CS: IC19.3 (CS1); also elsewhere on the board
!RESET: IC19.4 (RES), SJ4.2; also elsewhere on the board
!USB_RESET: SJ4.1, U$1.4 (!RST)
+5V: C18.1, C30.2, IC19.15 (VCC), J4.VBUS1 (VBUS), J4.VBUS2 (VBUS), JP11.4, R17.2, U$1.1 (VDD), U$1.11 (VUSB); also elsewhere on the board
A0: IC19.13 (RS0); also elsewhere on the board
A1: IC19.14 (RS1); also elsewhere on the board
ACIA_CSH: IC19.2 (CS0), R17.1
CTS: IC19.9 (CTS), JP11.7, JP12.2, SJ2.2
D0: IC19.18 (D0); also elsewhere on the board
D1: IC19.19 (D1); also elsewhere on the board
D2: IC19.20 (D2); also elsewhere on the board
D3: IC19.21 (D3); also elsewhere on the board
D4: IC19.22 (D4); also elsewhere on the board
D5: IC19.23 (D5); also elsewhere on the board
D6: IC19.24 (D6); also elsewhere on the board
D7: IC19.25 (D7); also elsewhere on the board
D+: J4.A6 (D+), J4.B6 (D+), U$1.13 (USB+)
D-: J4.A7 (D-), J4.B7 (D-), U$1.12 (USB-)
DTR: JP11.1; also elsewhere on the board
GND: C18.2, C29.1, C30.1, IC19.1 (GND), IC19.16 (DCD), IC19.17 (DSR), J4.GND, J4.GND2 (GND), J4.SHLD1 (SHLD), J4.SHLD2 (SHLD), J4.SHLD3 (SHLD), J4.SHLD4 (SHLD), J4.SHLD5 (SHLD), J4.SHLD6 (SHLD), J4.SHLD7 (SHLD), J4.SHLD8 (SHLD), JP11.6, SJ2.1, U$1.14 (GND); also elsewhere on the board
IRQ0: IC19.26 (IRQ); also elsewhere on the board
unnamed: C29.2, IC19.6 (XTL1), Q1.1
unnamed: IC19.7 (XTL2), Q1.2
PHI2: IC19.27 (PHI2); also elsewhere on the board
R/!W: IC19.28 (R/W); also elsewhere on the board
RTS: IC19.8 (RTS), JP12.1
RX: IC19.10 (TXD), JP11.2, U$1.5 (URX); also elsewhere on the board
TX: IC19.12 (RXD), JP11.3, U$1.6 (UTX); also elsewhere on the board

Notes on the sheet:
ACIA

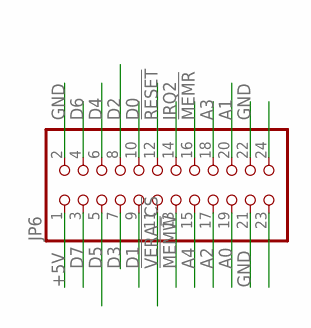
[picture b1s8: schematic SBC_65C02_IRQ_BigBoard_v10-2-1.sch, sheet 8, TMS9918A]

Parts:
JP6: PINHD-2X12; 2X12

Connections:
!MEMR: JP6.16; also elsewhere on the board
!MEMW: JP6.13; also elsewhere on the board
!RESET: JP6.12; also elsewhere on the board
!VERA_CS: JP6.11; also elsewhere on the board
+5V: JP6.1; also elsewhere on the board
A0: JP6.19; also elsewhere on the board
A1: JP6.20; also elsewhere on the board
A2: JP6.17; also elsewhere on the board
A3: JP6.18; also elsewhere on the board
A4: JP6.15; also elsewhere on the board
D0: JP6.10; also elsewhere on the board
D1: JP6.9; also elsewhere on the board
D2: JP6.8; also elsewhere on the board
D3: JP6.7; also elsewhere on the board
D4: JP6.6; also elsewhere on the board
D5: JP6.5; also elsewhere on the board
D6: JP6.4; also elsewhere on the board
D7: JP6.3; also elsewhere on the board
GND: JP6.2, JP6.21, JP6.22; also elsewhere on the board
IRQ2: JP6.14; also elsewhere on the board

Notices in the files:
Eagle/SBC_65C02_IRQ_BigBoard_v10-2-1.brd:
CC0-7X !VIA1_CS
parts and their libraries:
SparkFun-Connectors: Licensing: Creative Commons ShareAlike 4.0 International - https://creativecommons.org/licenses/by-sa/4.0
